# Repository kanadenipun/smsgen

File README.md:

smsgen
======

Sms generator using Arduino

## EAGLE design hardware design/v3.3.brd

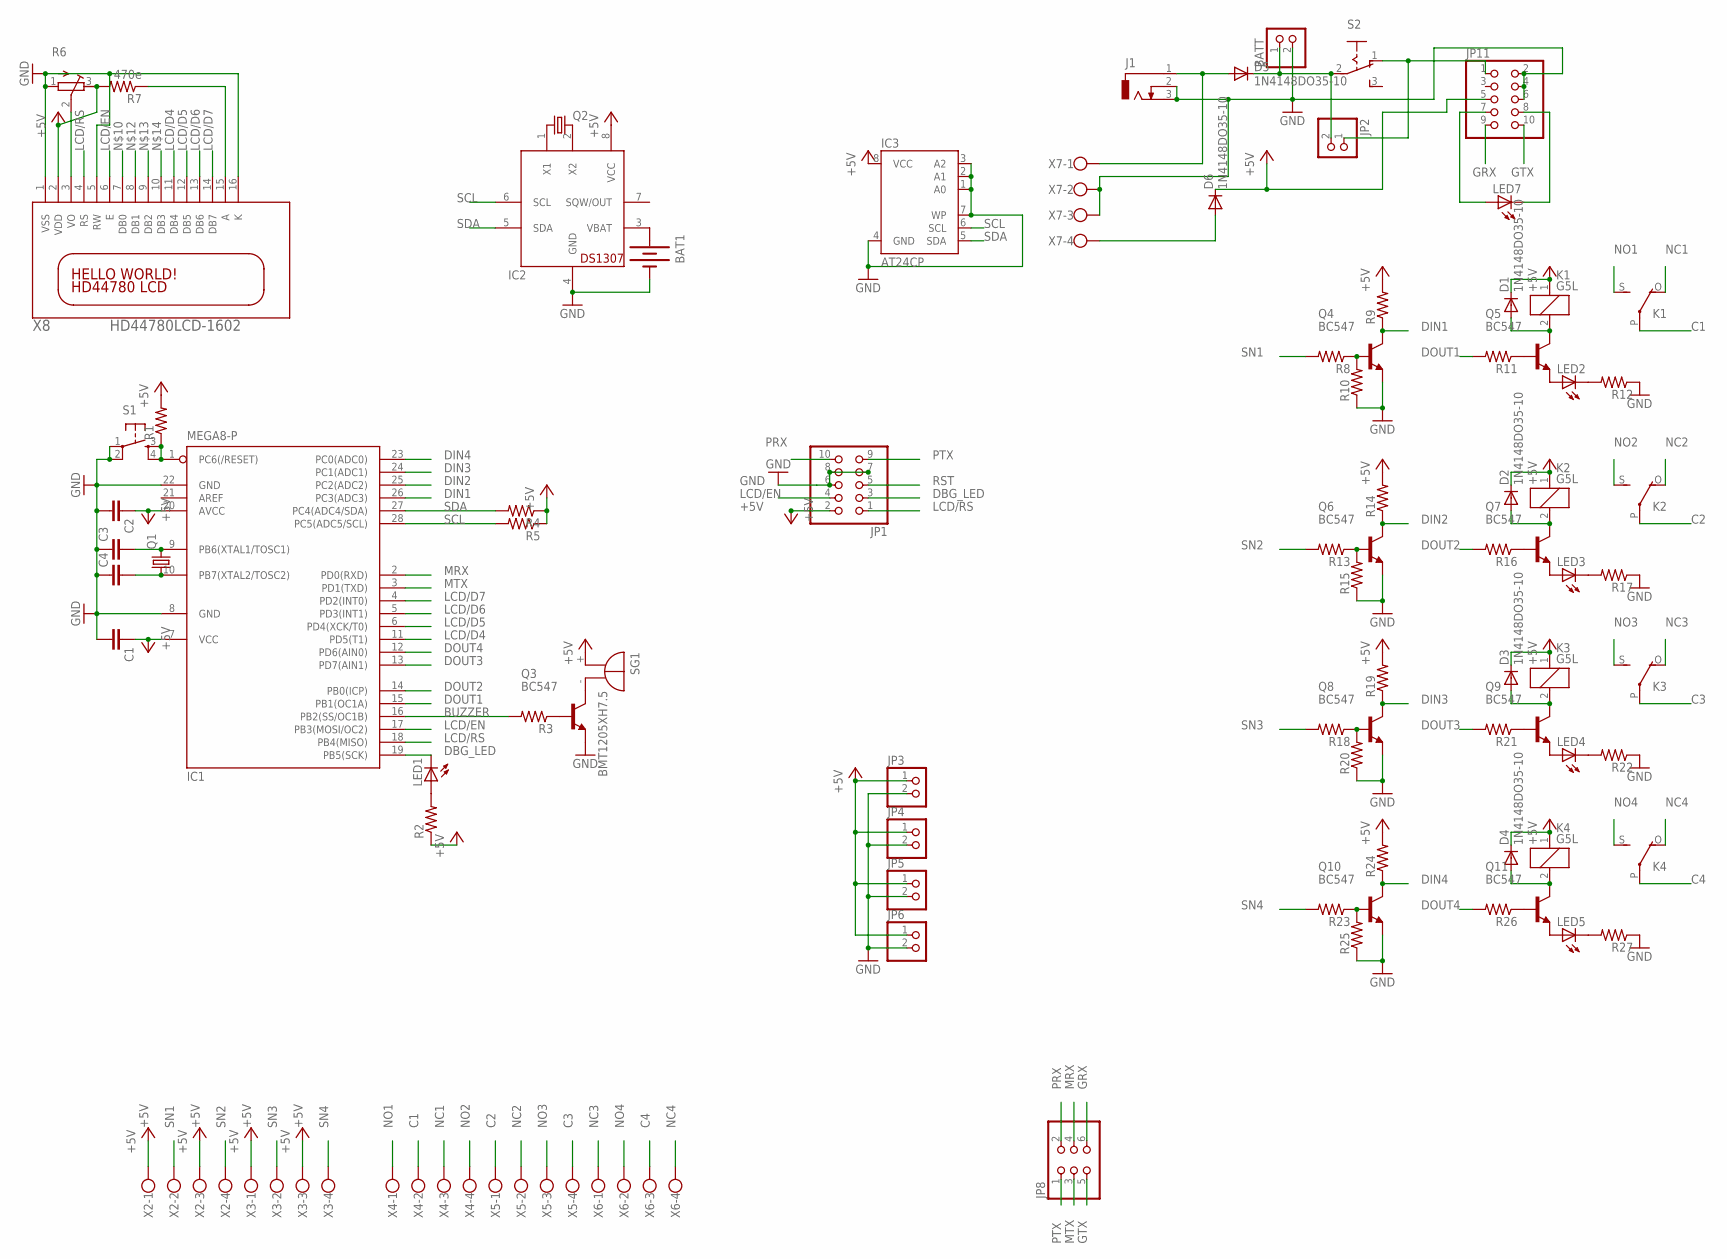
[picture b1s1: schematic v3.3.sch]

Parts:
BAT1: BATTERY20PTH; BATTCOM_20MM_PTH
BATT: PINHD-1X2; 1X02
C1, C2, C3, C4: C-EU050-025X075; C050-025X075
D1, D2, D3, D4, D5, D6: 1N4148DO35-10; DO35-10
IC1: MEGA8-P; DIL28-3
IC2: DS1307; DIL08
IC3: AT24CP; DIL08
J1: DCJ0303
JP1: PINHD-2X5/90; 2X05/90
JP2, JP3, JP4, JP5, JP6: PINHD-1X2; 1X02
JP8: PINHD-2X3/90; 2X03/90
JP11: PINHD-2X5; 2X05
K1, K2, K3, K4: G5L; G5LE
LED1, LED2, LED3, LED4, LED5, LED7: LED5MM
Q1: CRYSTALHC49U-V; HC49U-V
Q2: CRYSTALTC38H; TC38H
Q3, Q4, Q5, Q6, Q7, Q8, Q9, Q10, Q11: BC547; TO92
R1, R2, R3, R4, R5, R8, R9, R10, R11, R12, R13, R14, R15, R16, R17, R18, R19, R20, R21, R22, R23, R24, R25, R26, R27: R-US_0207/10; 0207/10
R6: R-TRIMM3339P; RTRIM3339P
R7: 470e; 0207/10
S1: TAC_SWITCHPTH; TACTILE-PTH
S2: M251
SG1: BMT1205XH7.5
X2, X3, X4, X5, X6, X7: W237-4
X8: HD44780LCD-1602; LCD1602

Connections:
+5V: C1.1, C2.1, D1.C, D2.C, D3.C, D4.C, D6.C, IC1.7 (VCC), IC1.20 (AVCC), IC2.8 (VCC), IC3.8 (VCC), JP1.2, JP3.1, JP4.1, JP5.1, JP6.1, JP11.5, K1.1, K2.1, K3.1, K4.1, R1.2, R2.1, R4.1, R5.1, R9.2, R14.2, R19.2, R24.2, SG1.+, X2.1, X2.3, X3.1, X3.3
BUZZER: IC1.16 (PB2(SS/OC1B)), R3.2
C1: K1.P, X4.2
C2: K2.P, X5.1
C3: K3.P, X5.4
C4: K4.P, X6.3
DBG_LED: IC1.19 (PB5(SCK)), JP1.3, LED1.K (C)
DIN1: IC1.26 (PC3(ADC3)), Q4.3 (C), R9.1
DIN2: IC1.25 (PC2(ADC2)), Q6.3 (C), R14.1
DIN3: IC1.24 (PC1(ADC1)), Q8.3 (C), R19.1
DIN4: IC1.23 (PC0(ADC0)), Q10.3 (C), R24.1
DOUT1: IC1.15 (PB1(OC1A)), R11.2
DOUT2: IC1.14 (PB0(ICP)), R16.2
DOUT3: IC1.13 (PD7(AIN1)), R21.2
DOUT4: IC1.12 (PD6(AIN0)), R26.2
GND: BAT1.2 (-), BATT.2, C1.2, C2.2, C3.1, C4.1, IC1.8 (GND), IC1.22 (GND), IC2.4 (GND), IC3.1 (A0), IC3.2 (A1), IC3.3 (A2), IC3.4 (GND), IC3.7 (WP), J1.2, J1.3, JP1.6, JP1.7, JP1.8, JP3.2, JP4.2, JP5.2, JP6.2, JP11.2, JP11.4, JP11.6, Q3.1 (E), Q4.1 (E), Q6.1 (E), Q8.1 (E), Q10.1 (E), R10.1, R12.1, R15.1, R17.1, R20.1, R22.1, R25.1, R27.1, S1.1, S1.2, X7.2, X7.3
GRX: JP8.6, JP11.9
GTX: JP8.5, JP11.10
LCD/D4: IC1.11 (PD5(T1)), X8.11 (DB4)
LCD/D5: IC1.6 (PD4(XCK/T0)), X8.12 (DB5)
LCD/D6: IC1.5 (PD3(INT1)), X8.13 (DB6)
LCD/D7: IC1.4 (PD2(INT0)), X8.14 (DB7)
LCD/EN: IC1.17 (PB3(MOSI/OC2)), JP1.4, X8.6 (E)
LCD/RS: IC1.18 (PB4(MISO)), JP1.1, X8.4 (RS)
MRX: IC1.2 (PD0(RXD)), JP8.4
MTX: IC1.3 (PD1(TXD)), JP8.3
unnamed: IC2.2 (X2), Q2.2
unnamed: R7.1, X8.15 (A)
unnamed: IC2.1 (X1), Q2.1
unnamed: LED1.A, R2.2
unnamed: C3.2, IC1.9 (PB6(XTAL1/TOSC1)), Q1.2
unnamed: C4.2, IC1.10 (PB7(XTAL2/TOSC2)), Q1.1
unnamed: Q3.2 (B), R3.1
unnamed: Q3.3 (C), SG1.-
unnamed: R6.2 (S), X8.3 (VO)
unnamed: BAT1.1 (+), IC2.3 (VBAT)
unnamed: D6.A, X7.4
unnamed: Q4.2 (B), R8.1, R10.2
unnamed: JP2.1, JP11.1, S2.1 (O)
unnamed: Q5.2 (B), R11.1
unnamed: LED2.A, Q5.1 (E)
unnamed: LED2.K (C), R12.2
unnamed: D1.A, K1.2, Q5.3 (C)
unnamed: D5.A, J1.1, X7.1
unnamed: BATT.1, D5.C, JP2.2, S2.2
unnamed: Q6.2 (B), R13.1, R15.2
unnamed: Q7.2 (B), R16.1
unnamed: LED3.A, Q7.1 (E)
unnamed: LED3.K (C), R17.2
unnamed: D2.A, K2.2, Q7.3 (C)
unnamed: Q8.2 (B), R18.1, R20.2
unnamed: Q9.2 (B), R21.1
unnamed: LED4.A, Q9.1 (E)
unnamed: LED4.K (C), R22.2
unnamed: D3.A, K3.2, Q9.3 (C)
unnamed: Q10.2 (B), R23.1, R25.2
unnamed: Q11.2 (B), R26.1
unnamed: LED5.A, Q11.1 (E)
unnamed: LED5.K (C), R27.2
unnamed: D4.A, K4.2, Q11.3 (C)
unnamed: JP11.7, LED7.A
unnamed: JP11.8, LED7.K (C)
NC1: K1.O, X4.3
NC2: K2.O, X5.2
NC3: K3.O, X6.1
NC4: K4.O, X6.4
NO1: K1.S, X4.1
NO2: K2.S, X4.4
NO3: K3.S, X5.3
NO4: K4.S, X6.2
PRX: JP1.10, JP8.2
PTX: JP1.9, JP8.1
RST: IC1.1 (PC6(/RESET)), JP1.5, R1.1, S1.3, S1.4
SCL: IC1.28 (PC5(ADC5/SCL)), IC2.6 (SCL), IC3.6 (SCL), R5.2
SDA: IC1.27 (PC4(ADC4/SDA)), IC2.5 (SDA), IC3.5 (SDA), R4.2
SN1: R8.2, X2.2
SN2: R13.2, X2.4
SN3: R18.2, X3.2
SN4: R23.2, X3.4
VDD: R6.3 (E), R7.2, X8.2 (VDD)
VSS: R6.1 (A), X8.1 (VSS), X8.5 (RW), X8.16 (K)

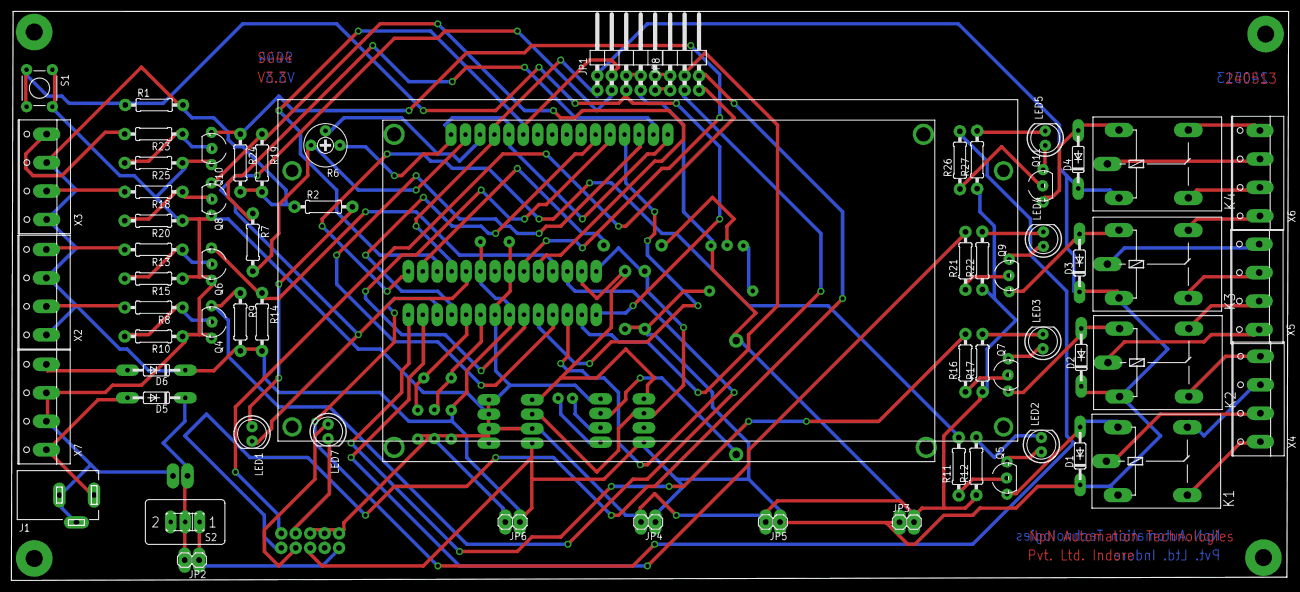
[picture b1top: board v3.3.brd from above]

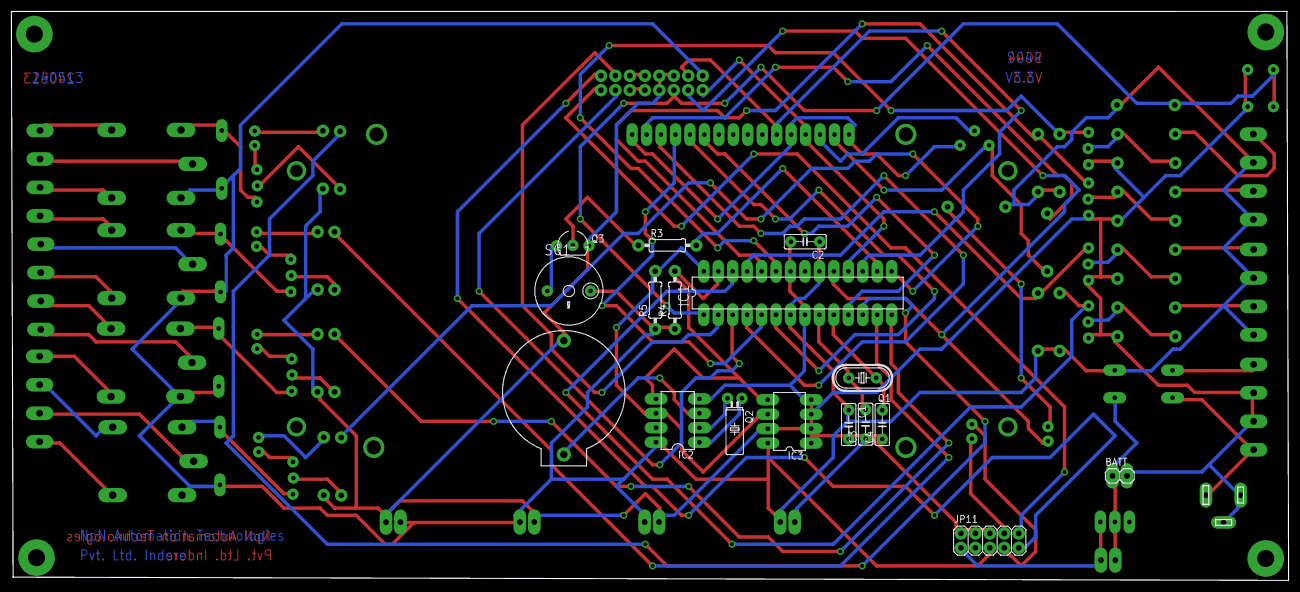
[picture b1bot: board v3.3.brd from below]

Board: 2 copper layers, 224.4 x 100.0 mm, 83 parts (17 on the bottom side), 81 nets.

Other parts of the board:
U$1: SIM300_OUTLINE

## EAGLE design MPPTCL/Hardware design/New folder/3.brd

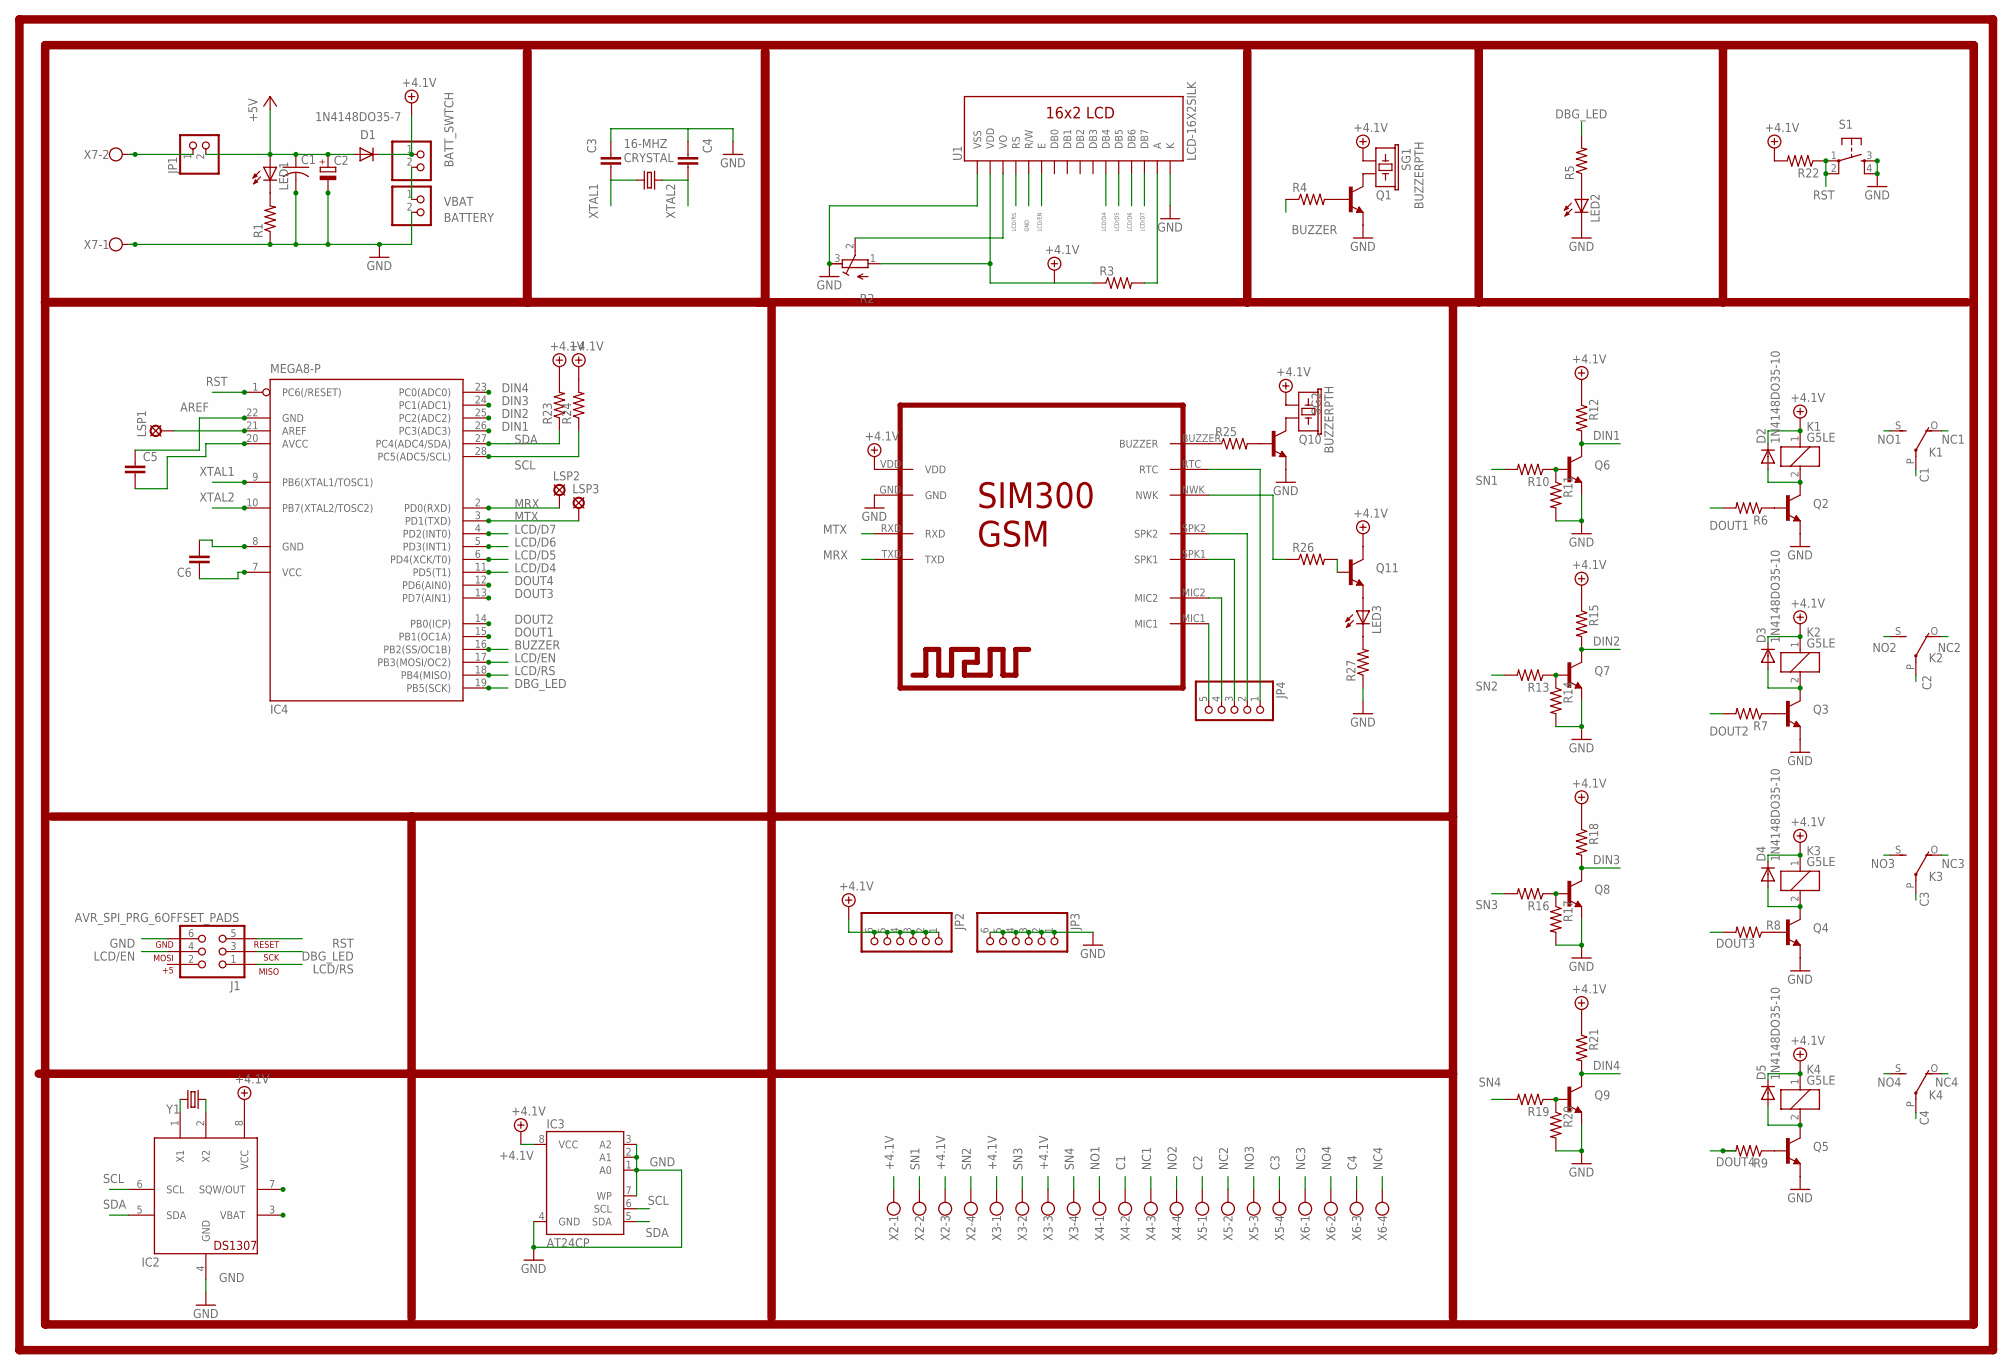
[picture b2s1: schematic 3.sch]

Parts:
BATTERY: PINHD-1X2; 1X02
BATT_SWTCH: PINHD-1X2; 1X02
C1: C-US050-035X075; C050-035X075
C2: CPOL-EUE3.5-8; E3,5-8
C3, C4, C5, C6: CAPPTH1; CAP-PTH-5MM
CRYSTAL: 16-MHZ; HC49U-V
D1: 1N4148DO35-7; DO35-7
D2, D3, D4, D5: 1N4148DO35-10; DO35-10
IC2: DS1307; DIL08
IC3: AT24CP; DIL08
IC4: MEGA8-P; DIL28-3
J1: AVR_SPI_PRG_6OFFSET_PADS; 2X3_OFFSET
JP1: PINHD-1X2; 1X02
JP2, JP3: PINHD-1X6; 1X06
JP4: PINHD-1X5; 1X05
K1, K2, K3, K4: G5LE
LED1, LED2, LED3: LED5MM
LSP1: LSP11
LSP2, LSP3: MCS10B
Q1, Q2, Q3, Q4, Q5, Q6, Q7, Q8, Q9, Q10, Q11: TRANSISTOR_NPNTO-92-AMMO; TO-92-AMMO
R1, R4, R5, R6, R7, R8, R9, R10, R11, R12, R13, R14, R15, R16, R17, R18, R19, R20, R21, R22, R23, R24, R25, R26, R27: RESISTORPTH-1/2W; AXIAL-0.5
R2: R-TRIMM3339P; RTRIM3339P
R3: RESISTORPTH-2W; AXIAL-0.8
S1: TAC_SWITCHPTH; TACTILE-PTH
SG1, SG2: BUZZERPTH; BUZZER-12MM
U1: LCD-16X2SILK; LCD-16X2
U$1: SIM300; 1X10
X2, X3, X4, X5, X6: W237-4
X7: W237-102
Y1: CRYSTALTC38H; TC38H

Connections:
+4.1V: BATT_SWTCH.1, C5.2, C6.1, D1.C, D2.C, D3.C, D4.C, D5.C, IC2.8 (VCC), IC3.8 (VCC), IC4.7 (VCC), IC4.20 (AVCC), JP2.1, JP2.2, JP2.3, JP2.4, JP2.5, JP2.6, K1.1, K2.1, K3.1, K4.1, Q11.3 (C), R2.1 (A), R3.P$1 (1), R12.P$1 (1), R15.P$1 (1), R18.P$1 (1), R21.P$1 (1), R22.P$2 (2), R23.P$2 (2), R24.P$2 (2), SG1.+ (1), SG2.+ (1), U1.2 (VDD), U$1.VDD, X2.1, X2.3, X3.1, X3.3
+5V: C1.1, C2.+, D1.A, JP1.2, LED1.A
AREF: IC4.21 (AREF), LSP1.MP
BUZZER: IC4.16 (PB2(SS/OC1B)), R4.P$1 (1)
C1: K1.P, X4.2
C2: K2.P, X5.1
C3: K3.P, X5.4
C4: K4.P, X6.3
DBG_LED: IC4.19 (PB5(SCK)), J1.3, R5.P$2 (2)
DIN1: IC4.26 (PC3(ADC3)), Q6.3 (C), R12.P$2 (2)
DIN2: IC4.25 (PC2(ADC2)), Q7.3 (C), R15.P$2 (2)
DIN3: IC4.24 (PC1(ADC1)), Q8.3 (C), R18.P$2 (2)
DIN4: IC4.23 (PC0(ADC0)), Q9.3 (C), R21.P$2 (2)
DOUT1: IC4.15 (PB1(OC1A)), R6.P$2 (2)
DOUT2: IC4.14 (PB0(ICP)), R7.P$2 (2)
DOUT3: IC4.13 (PD7(AIN1)), R8.P$2 (2)
DOUT4: IC4.12 (PD6(AIN0)), R9.P$2 (2)
GND: BATTERY.2, C1.2, C2.-, C3.1, C4.1, C5.1, C6.2, IC2.4 (GND), IC3.1 (A0), IC3.2 (A1), IC3.3 (A2), IC3.4 (GND), IC3.7 (WP), IC4.8 (GND), IC4.22 (GND), J1.6, JP3.1, JP3.2, JP3.3, JP3.4, JP3.5, JP3.6, LED2.K (C), Q1.1 (E), Q2.1 (E), Q3.1 (E), Q4.1 (E), Q5.1 (E), Q6.1 (E), Q7.1 (E), Q8.1 (E), Q9.1 (E), Q10.1 (E), R1.P$1 (1), R2.3 (E), R11.P$2 (2), R14.P$2 (2), R17.P$2 (2), R20.P$2 (2), R27.P$1 (1), S1.3, S1.4, U1.1 (VSS), U1.5 (R/W), U1.16 (K), U$1.GND, X7.1
LCD/D4: IC4.11 (PD5(T1)), U1.11 (DB4)
LCD/D5: IC4.6 (PD4(XCK/T0)), U1.12 (DB5)
LCD/D6: IC4.5 (PD3(INT1)), U1.13 (DB6)
LCD/D7: IC4.4 (PD2(INT0)), U1.14 (DB7)
LCD/EN: IC4.17 (PB3(MOSI/OC2)), J1.4, U1.6 (E)
LCD/RS: IC4.18 (PB4(MISO)), J1.1, U1.4 (RS)
MRX: IC4.2 (PD0(RXD)), LSP2.MP, U$1.TXD
MTX: IC4.3 (PD1(TXD)), LSP3.MP, U$1.RXD
unnamed: JP1.1, X7.2
unnamed: LED1.K (C), R1.P$2 (2)
unnamed: LED3.A, Q11.1 (E)
unnamed: R2.2 (S), U1.3 (VO)
unnamed: Q1.3 (C), SG1.- (2)
unnamed: Q1.2 (B), R4.P$2 (2)
unnamed: LED2.A, R5.P$1 (1)
unnamed: D2.A, K1.2, Q2.3 (C)
unnamed: Q2.2 (B), R6.P$1 (1)
unnamed: D3.A, K2.2, Q3.3 (C)
unnamed: Q3.2 (B), R7.P$1 (1)
unnamed: R3.P$2 (2), U1.15 (A)
unnamed: D4.A, K3.2, Q4.3 (C)
unnamed: Q4.2 (B), R8.P$1 (1)
unnamed: D5.A, K4.2, Q5.3 (C)
unnamed: Q5.2 (B), R9.P$1 (1)
unnamed: Q6.2 (B), R10.P$1 (1), R11.P$1 (1)
unnamed: JP4.5, U$1.MIC1
unnamed: JP4.4, U$1.MIC2
unnamed: JP4.3, U$1.SPK1
unnamed: Q7.2 (B), R13.P$1 (1), R14.P$1 (1)
unnamed: JP4.2, U$1.SPK2
unnamed: JP4.1, U$1.RTC
unnamed: Q8.2 (B), R16.P$1 (1), R17.P$1 (1)
unnamed: IC2.1 (X1), Y1.2
unnamed: R25.P$1 (1), U$1.BUZZER
unnamed: Q9.2 (B), R19.P$1 (1), R20.P$1 (1)
unnamed: IC2.2 (X2), Y1.1
unnamed: Q10.2 (B), R25.P$2 (2)
unnamed: Q10.3 (C), SG2.- (2)
unnamed: Q11.2 (B), R26.P$2 (2)
unnamed: LED3.K (C), R27.P$2 (2)
unnamed: R26.P$1 (1), U$1.NWK
NC1: K1.O, X4.3
NC2: K2.O, X5.2
NC3: K3.O, X6.1
NC4: K4.O, X6.4
NO1: K1.S, X4.1
NO2: K2.S, X4.4
NO3: K3.S, X5.3
NO4: K4.S, X6.2
RST: IC4.1 (PC6(/RESET)), J1.5, R22.P$1 (1), S1.1, S1.2
SCL: IC2.6 (SCL), IC3.6 (SCL), IC4.28 (PC5(ADC5/SCL)), R24.P$1 (1)
SDA: IC2.5 (SDA), IC3.5 (SDA), IC4.27 (PC4(ADC4/SDA)), R23.P$1 (1)
SN1: R10.P$2 (2), X2.2
SN2: R13.P$2 (2), X2.4
SN3: R16.P$2 (2), X3.2
SN4: R19.P$2 (2), X3.4
VBAT: BATTERY.1, BATT_SWTCH.2, IC2.3 (VBAT)
XTAL1: C3.2, CRYSTAL.1, IC4.9 (PB6(XTAL1/TOSC1))
XTAL2: C4.2, CRYSTAL.2, IC4.10 (PB7(XTAL2/TOSC2))

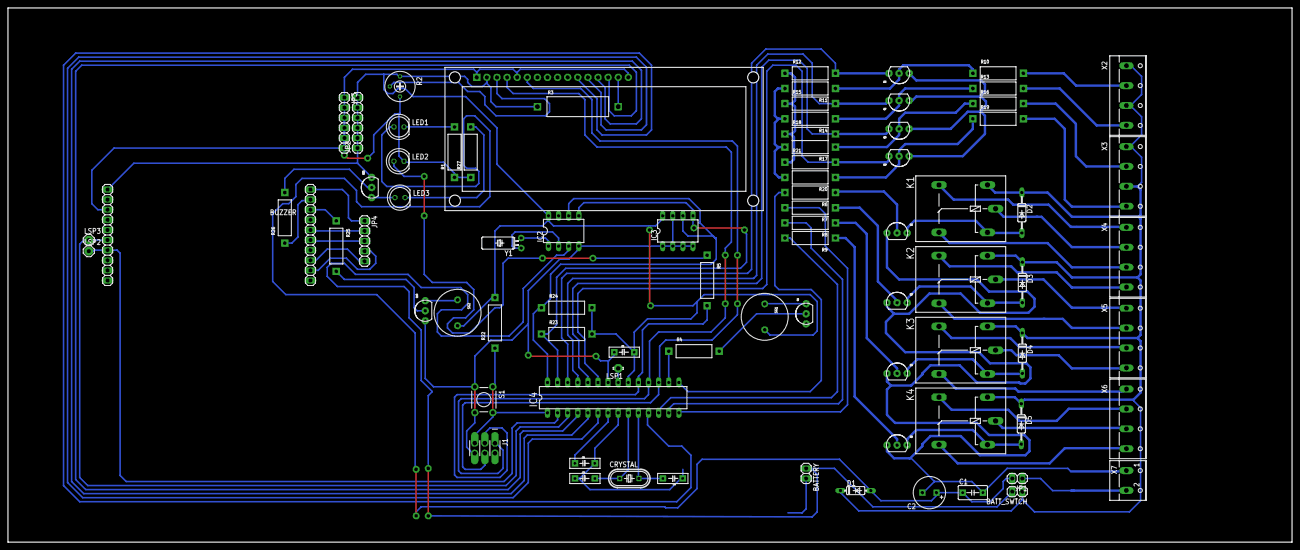
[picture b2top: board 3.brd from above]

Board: 2 copper layers, 322.8 x 134.3 mm, 82 parts (0 on the bottom side), 77 nets.

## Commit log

2013-09-24 files added
2013-09-24 added newer versions

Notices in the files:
parts and their libraries:
SparkFun_NPN: Licensing: CC v3.0 Share-Alike You are welcome to use this library for commercial purposes.
